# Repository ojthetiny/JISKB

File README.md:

# JISKB

Layout by the ever so wonderful Tesla

don't ask me what the fuck this is or why it exists, not my idea.
it's a jis hhkb 35% board or something, I was bored OK

pics of the fancy routing or whatever

pics of the front if you give a shit, you probably don't

All the files are in the folders, including bom and pos files for assembly by jlc. if you wanna get this made you look for them yourself, I'm not helping you, use your noggin'

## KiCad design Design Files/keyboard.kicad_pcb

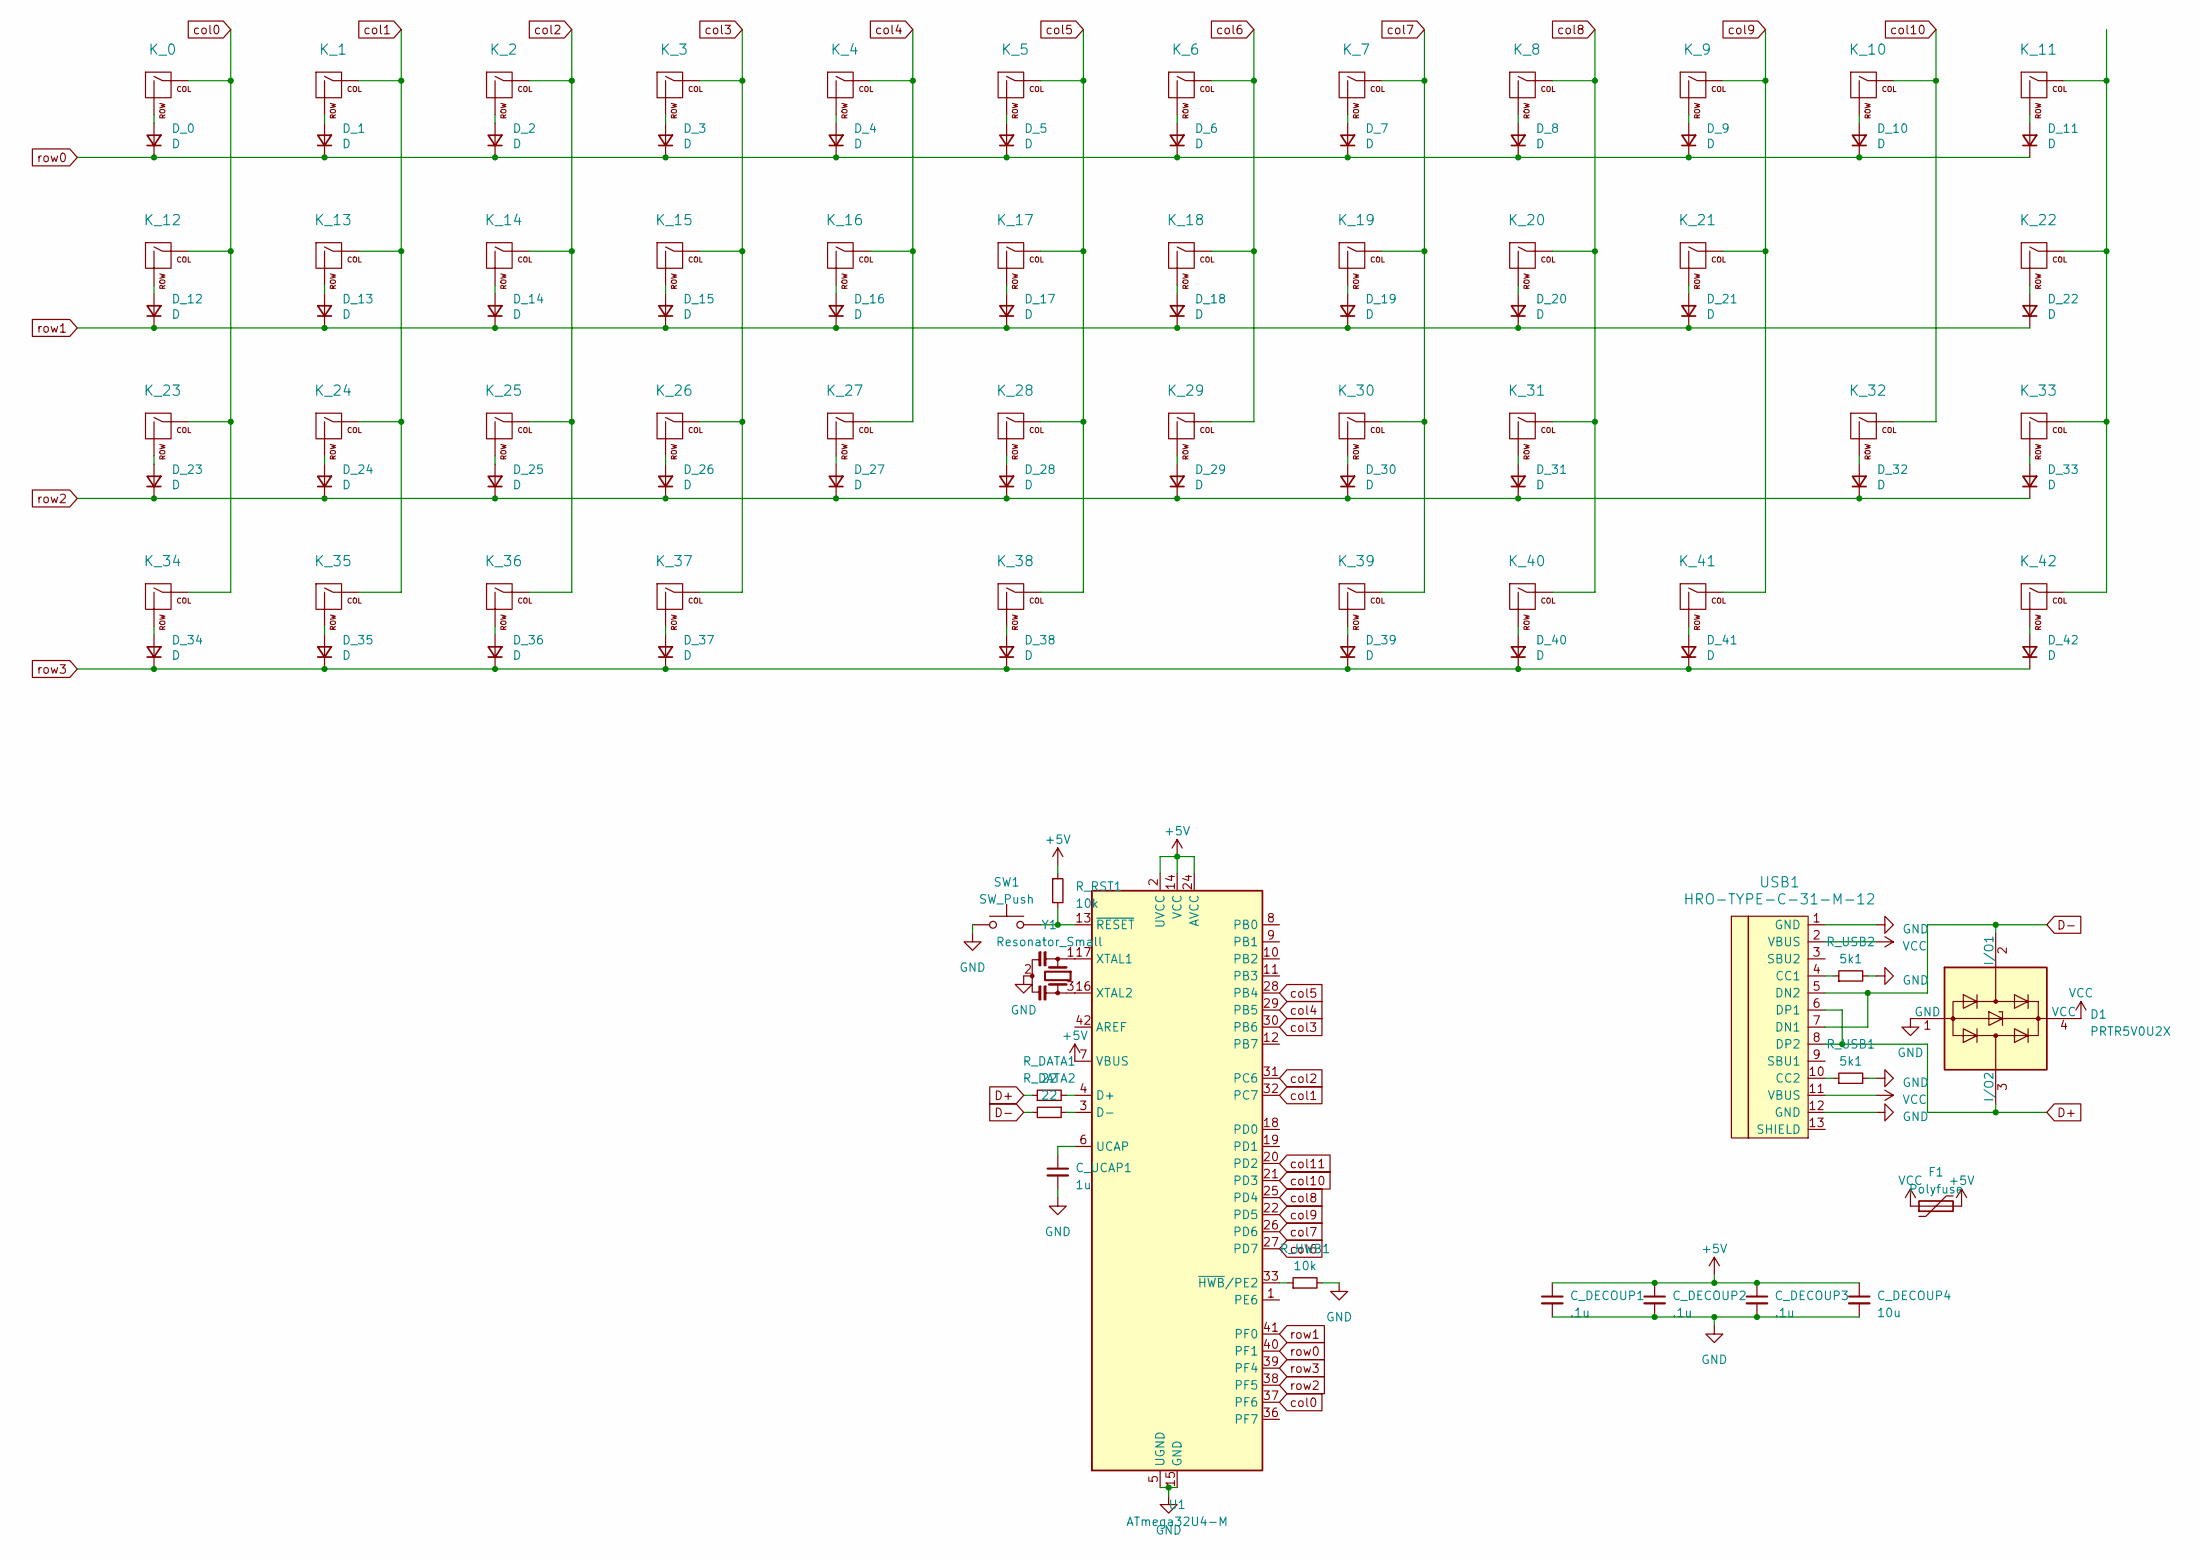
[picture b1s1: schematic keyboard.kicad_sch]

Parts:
C_DECOUP1, C_DECOUP2, C_DECOUP3: .1u; C_0402_1005Metric
C_DECOUP4: 10u; C_0402_1005Metric
C_UCAP1: 1u; C_0402_1005Metric
D1: PRTR5V0U2X; SOT-143
D_0, D_1, D_2, D_3, D_4, D_5, D_6, D_7, D_8, D_9, D_10, D_11, D_12, D_13, D_14, D_15, D_16, D_17, D_18, D_19, D_20, D_21, D_22, D_23, D_24, D_25, D_26, D_27, D_28, D_29, D_30, D_31, D_32, D_33, D_34, D_35, D_36, D_37, D_38, D_39, D_40, D_41, D_42: D; D_SOD-123
F1: Polyfuse; Fuse_0805
K_0, K_1, K_2, K_3, K_4, K_5, K_6, K_7, K_8, K_9, K_10, K_11, K_13, K_14, K_15, K_16, K_17, K_18, K_19, K_20, K_21, K_24, K_25, K_26, K_27, K_28, K_29, K_30, K_32, K_33, K_35, K_37, K_39, K_40, K_41, K_42: KEYSW; MX-1U-NoLED
K_12, K_31: KEYSW; MX-1.25U-NoLED
K_22, K_23: KEYSW; MX-1.75U-NoLED
K_34, K_36: KEYSW; MX-1.5U-NoLED
K_38: KEYSW; MX-2.75U-NoLED
R_DATA1, R_DATA2: 22; R_0402_1005Metric
R_HWB1: 10k; R_0402_1005Metric
R_RST1: 10k; R_0402_1005Metric
R_USB1, R_USB2: 5k1; R_0402_1005Metric
SW1: SW_Push; SKQG-1155865
U1: ATmega32U4-M; QFN-44-1EP_7x7mm_P0.5mm_EP5.2x5.2mm
USB1: HRO-TYPE-C-31-M-12; HRO-TYPE-C-31-M-12-Assembly
Y1: Resonator_Small; Resonator_SMD_Murata_CSTxExxV-3Pin_3.0x1.1mm

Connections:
+5V: C_DECOUP1.1, C_DECOUP2.1, C_DECOUP3.1, C_DECOUP4.1, F1.2, R_RST1.1, U1.2 (UVCC), U1.7 (VBUS), U1.14 (VCC), U1.24 (AVCC), U1.34 (VCC), U1.44 (AVCC)
D+: D1.3 (I/O2), R_DATA1.1, USB1.6 (DP1), USB1.8 (DP2)
D-: D1.2 (I/O1), R_DATA2.2, USB1.5 (DN2), USB1.7 (DN1)
GND: C_DECOUP1.2, C_DECOUP2.2, C_DECOUP3.2, C_DECOUP4.2, C_UCAP1.2, D1.1 (GND), R_HWB1.2, R_USB1.2, R_USB2.2, SW1.1, U1.5 (UGND), U1.15 (GND), U1.23 (GND), U1.35 (GND), U1.43 (GND), U1.45 (GND), USB1.1 (GND), USB1.12 (GND), Y1.2
unnamed: C_UCAP1.1, U1.6 (UCAP)
unnamed: D_0.2 (A), K_0.2 (ROW)
unnamed: D_1.2 (A), K_1.2 (ROW)
unnamed: D_2.2 (A), K_2.2 (ROW)
unnamed: D_3.2 (A), K_3.2 (ROW)
unnamed: D_4.2 (A), K_4.2 (ROW)
unnamed: D_5.2 (A), K_5.2 (ROW)
unnamed: D_6.2 (A), K_6.2 (ROW)
unnamed: D_7.2 (A), K_7.2 (ROW)
unnamed: D_8.2 (A), K_8.2 (ROW)
unnamed: D_9.2 (A), K_9.2 (ROW)
unnamed: D_10.2 (A), K_10.2 (ROW)
unnamed: D_11.2 (A), K_11.2 (ROW)
unnamed: D_12.2 (A), K_12.2 (ROW)
unnamed: D_13.2 (A), K_13.2 (ROW)
unnamed: D_14.2 (A), K_14.2 (ROW)
unnamed: D_15.2 (A), K_15.2 (ROW)
unnamed: D_16.2 (A), K_16.2 (ROW)
unnamed: D_17.2 (A), K_17.2 (ROW)
unnamed: D_18.2 (A), K_18.2 (ROW)
unnamed: D_19.2 (A), K_19.2 (ROW)
unnamed: D_20.2 (A), K_20.2 (ROW)
unnamed: D_21.2 (A), K_21.2 (ROW)
unnamed: D_22.2 (A), K_22.2 (ROW)
unnamed: D_23.2 (A), K_23.2 (ROW)
unnamed: D_24.2 (A), K_24.2 (ROW)
unnamed: D_25.2 (A), K_25.2 (ROW)
unnamed: D_26.2 (A), K_26.2 (ROW)
unnamed: D_27.2 (A), K_27.2 (ROW)
unnamed: D_28.2 (A), K_28.2 (ROW)
unnamed: D_29.2 (A), K_29.2 (ROW)
unnamed: D_30.2 (A), K_30.2 (ROW)
unnamed: D_31.2 (A), K_31.2 (ROW)
unnamed: D_32.2 (A), K_32.2 (ROW)
unnamed: D_33.2 (A), K_33.2 (ROW)
unnamed: D_34.2 (A), K_34.2 (ROW)
unnamed: D_35.2 (A), K_35.2 (ROW)
unnamed: D_36.2 (A), K_36.2 (ROW)
unnamed: D_37.2 (A), K_37.2 (ROW)
unnamed: D_38.2 (A), K_38.2 (ROW)
unnamed: D_39.2 (A), K_39.2 (ROW)
unnamed: D_40.2 (A), K_40.2 (ROW)
unnamed: D_41.2 (A), K_41.2 (ROW)
unnamed: D_42.2 (A), K_42.2 (ROW)
unnamed: R_DATA1.2, U1.4 (D+)
unnamed: R_DATA2.1, U1.3 (D-)
unnamed: R_HWB1.1, U1.33 (~HWB~/PE2)
unnamed: R_RST1.2, SW1.2, U1.13 (~RESET)
unnamed: R_USB1.1, USB1.10 (CC2)
unnamed: R_USB2.1, USB1.4 (CC1)
unnamed: U1.16 (XTAL2), Y1.3
unnamed: U1.17 (XTAL1), Y1.1
VCC: D1.4 (VCC), F1.1, USB1.2 (VBUS), USB1.11 (VBUS)
col0: K_0.1 (COL), K_12.1 (COL), K_23.1 (COL), K_34.1 (COL), U1.37 (PF6)
col1: K_1.1 (COL), K_13.1 (COL), K_24.1 (COL), K_35.1 (COL), U1.32 (PC7)
col2: K_2.1 (COL), K_14.1 (COL), K_25.1 (COL), K_36.1 (COL), U1.31 (PC6)
col3: K_3.1 (COL), K_15.1 (COL), K_26.1 (COL), K_37.1 (COL), U1.30 (PB6)
col4: K_4.1 (COL), K_16.1 (COL), K_27.1 (COL), U1.29 (PB5)
col5: K_5.1 (COL), K_17.1 (COL), K_28.1 (COL), K_38.1 (COL), U1.28 (PB4)
col6: K_6.1 (COL), K_18.1 (COL), K_29.1 (COL), U1.27 (PD7)
col7: K_7.1 (COL), K_19.1 (COL), K_30.1 (COL), K_39.1 (COL), U1.26 (PD6)
col8: K_8.1 (COL), K_20.1 (COL), K_31.1 (COL), K_40.1 (COL), U1.25 (PD4)
col9: K_9.1 (COL), K_21.1 (COL), K_41.1 (COL), U1.22 (PD5)
col10: K_10.1 (COL), K_32.1 (COL), U1.21 (PD3)
row0: D_0.1 (K), D_1.1 (K), D_2.1 (K), D_3.1 (K), D_4.1 (K), D_5.1 (K), D_6.1 (K), D_7.1 (K), D_8.1 (K), D_9.1 (K), D_10.1 (K), D_11.1 (K), U1.40 (PF1)
row1: D_12.1 (K), D_13.1 (K), D_14.1 (K), D_15.1 (K), D_16.1 (K), D_17.1 (K), D_18.1 (K), D_19.1 (K), D_20.1 (K), D_21.1 (K), D_22.1 (K), U1.41 (PF0)
row2: D_23.1 (K), D_24.1 (K), D_25.1 (K), D_26.1 (K), D_27.1 (K), D_28.1 (K), D_29.1 (K), D_30.1 (K), D_31.1 (K), D_32.1 (K), D_33.1 (K), U1.38 (PF5)
row3: D_34.1 (K), D_35.1 (K), D_36.1 (K), D_37.1 (K), D_38.1 (K), D_39.1 (K), D_40.1 (K), D_41.1 (K), D_42.1 (K), U1.39 (PF4)

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
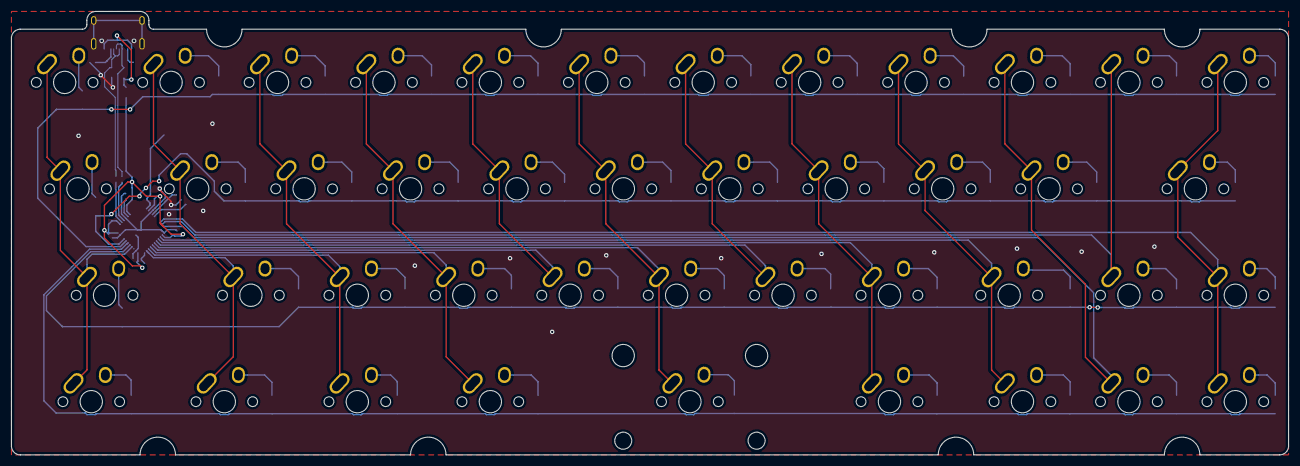
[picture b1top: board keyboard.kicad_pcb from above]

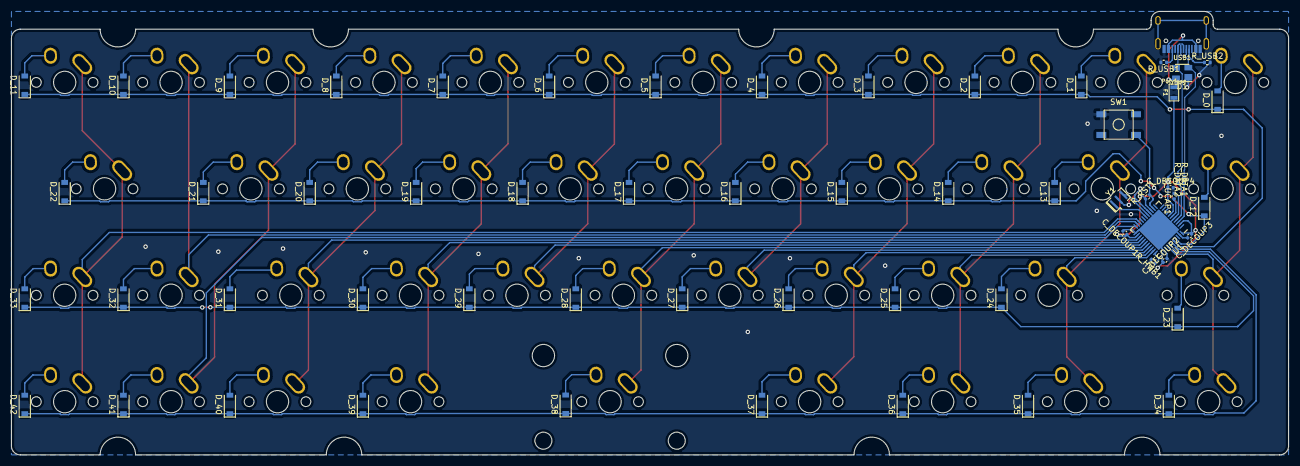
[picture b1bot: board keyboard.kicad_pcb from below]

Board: 2 copper layers, 228.6 x 79.4 mm, 103 parts (60 on the bottom side), 73 nets.

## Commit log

2021-05-11 add layout screenshot
2021-05-11 moved images to a folder
2021-05-11 renamed image for readme
